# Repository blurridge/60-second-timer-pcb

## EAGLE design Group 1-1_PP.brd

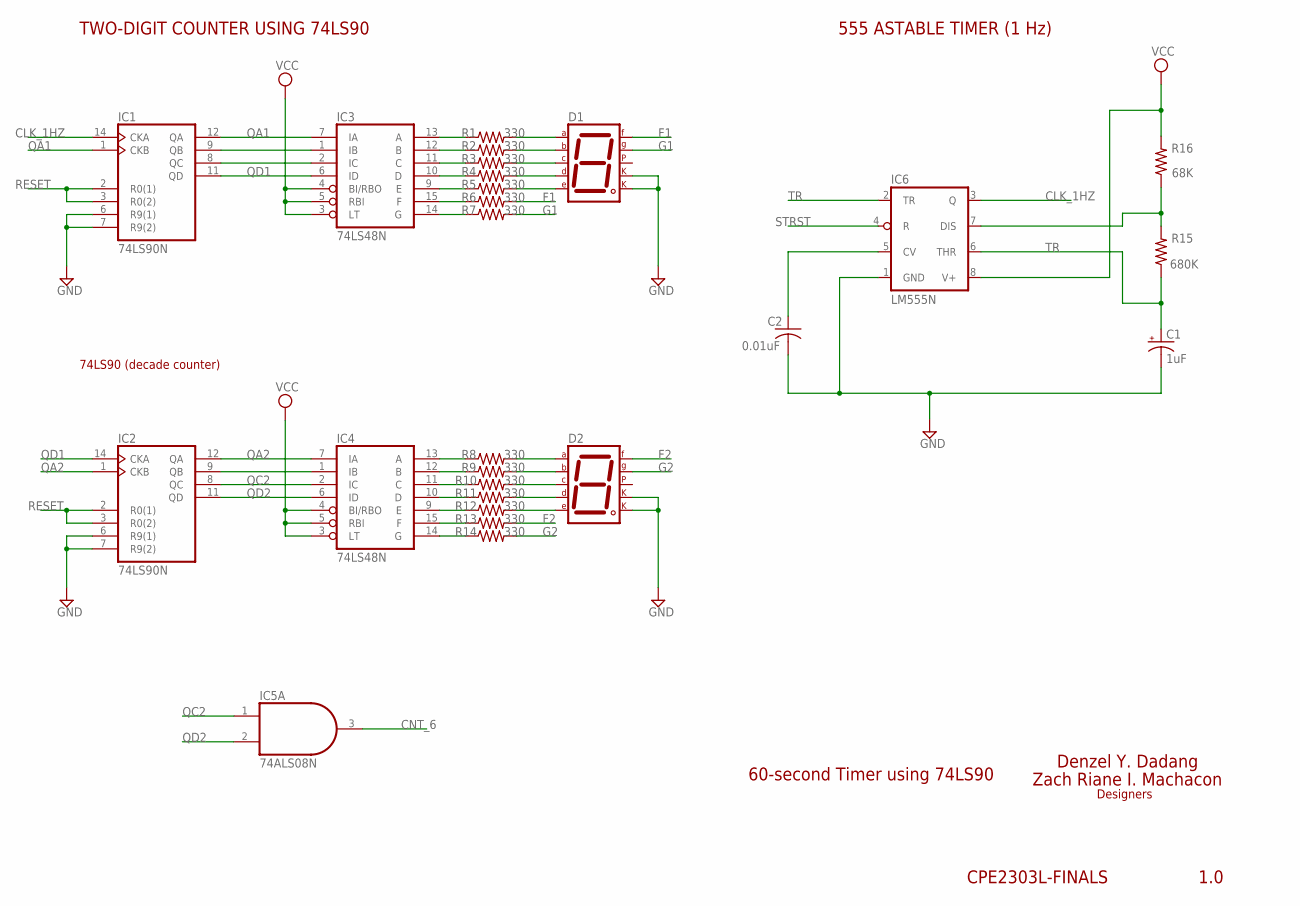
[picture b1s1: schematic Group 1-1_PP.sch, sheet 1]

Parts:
C1: 1uF; E1,8-4
C2: 0.01uF; C025-025X050
D1, D2: 7SEG-CK; 7SEG-13
IC1, IC2: 74LS90N; DIL14
IC3, IC4: 74LS48N; DIL16
IC5: 74ALS08N; DIL14
IC6: LM555N; DIL08
R1, R2, R3, R4, R5, R6, R7, R8, R9, R10, R11, R12, R13, R14: 330; 0204/7
R15: 680K; 0204/7
R16: 68K; 0204/7

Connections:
CLK_1HZ: IC1.14 (CKA), IC6.3 (Q)
CNT_6: IC5.3 (O); also elsewhere on the board
F1: D1.9 (F), R6.2
F2: D2.9 (F), R13.2
G1: D1.10 (G), R7.2
G2: D2.10 (G), R14.2
GND: C1.-, C2.2, D1.3 (CK1), D1.8 (CK2), D2.3 (CK1), D2.8 (CK2), IC1.6 (R9(1)), IC1.7 (R9(2)), IC1.10 (GND), IC2.6 (R9(1)), IC2.7 (R9(2)), IC2.10 (GND), IC3.8 (GND), IC4.8 (GND), IC5.7 (GND), IC6.1 (GND); also elsewhere on the board
unnamed: IC3.13 (A), R1.1
unnamed: IC6.7 (DIS), R15.2, R16.1
unnamed: IC1.9 (QB), IC3.1 (IB)
unnamed: C2.1, IC6.5 (CV)
unnamed: IC1.8 (QC), IC3.2 (IC)
unnamed: IC3.12 (B), R2.1
unnamed: IC3.11 (C), R3.1
unnamed: IC3.10 (D), R4.1
unnamed: IC3.9 (E), R5.1
unnamed: IC3.15 (F), R6.1
unnamed: IC3.14 (G), R7.1
unnamed: IC4.13 (A), R8.1
unnamed: IC2.9 (QB), IC4.1 (IB)
unnamed: D1.1 (E), R5.2
unnamed: D1.2 (D), R4.2
unnamed: D1.4 (C), R3.2
unnamed: D1.6 (B), R2.2
unnamed: D1.7 (A), R1.2
unnamed: IC4.12 (B), R9.1
unnamed: IC4.11 (C), R10.1
unnamed: IC4.10 (D), R11.1
unnamed: IC4.9 (E), R12.1
unnamed: IC4.15 (F), R13.1
unnamed: IC4.14 (G), R14.1
unnamed: D2.7 (A), R8.2
unnamed: D2.6 (B), R9.2
unnamed: D2.4 (C), R10.2
unnamed: D2.2 (D), R11.2
unnamed: D2.1 (E), R12.2
QA1: IC1.1 (CKB), IC1.12 (QA), IC3.7 (IA)
QA2: IC2.1 (CKB), IC2.12 (QA), IC4.7 (IA)
QC2: IC2.8 (QC), IC4.2 (IC), IC5.1 (I0)
QD1: IC1.11 (QD), IC2.14 (CKA), IC3.6 (ID)
QD2: IC2.11 (QD), IC4.6 (ID), IC5.2 (I1)
RESET: IC1.2 (R0(1)), IC1.3 (R0(2)), IC2.2 (R0(1)), IC2.3 (R0(2)); also elsewhere on the board
STRST: IC6.4 (R); also elsewhere on the board
TR: C1.+, IC6.2 (TR), IC6.6 (THR), R15.1
VCC: IC1.5 (VCC), IC2.5 (VCC), IC3.3 (LT), IC3.4 (BI/RBO), IC3.5 (RBI), IC3.16 (VCC), IC4.3 (LT), IC4.4 (BI/RBO), IC4.5 (RBI), IC4.16 (VCC), IC5.14 (VCC), IC6.8 (V+), R16.2; also elsewhere on the board

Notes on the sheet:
60-second Timer using 74LS90
Zach Riane I. Machacon
Denzel Y. Dadang
Designers
CPE2303L-FINALS
1.0
555 ASTABLE TIMER (1 Hz)
TWO-DIGIT COUNTER USING 74LS90
74LS90 (decade counter)

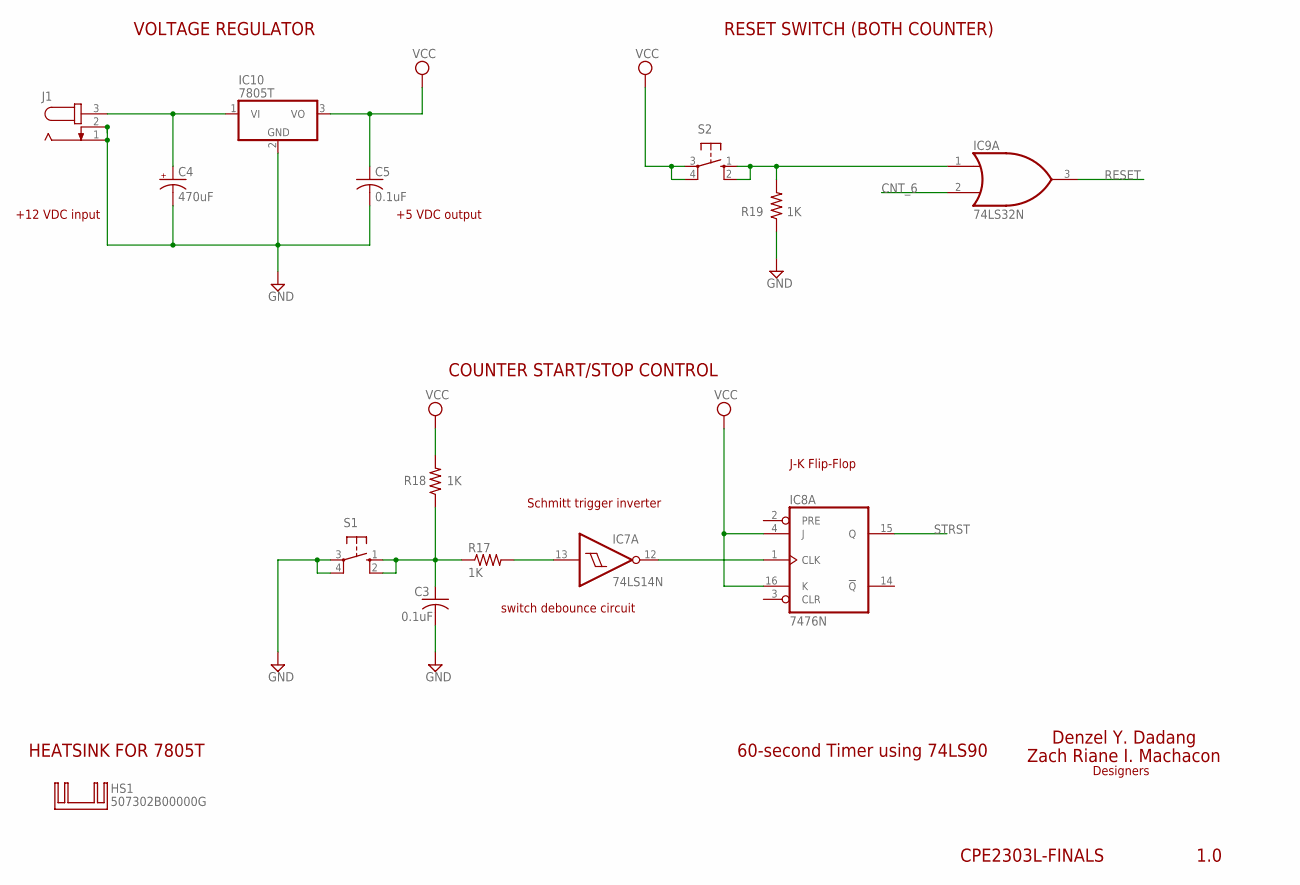
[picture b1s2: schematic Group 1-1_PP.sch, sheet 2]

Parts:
C3, C5: 0.1uF; C025-025X050
C4: 470uF; E1,8-4
HS1: 507302B00000G; TO-220H
IC7: 74LS14N; DIL14
IC8: 7476N; DIL16
IC9: 74LS32N; DIL14
IC10: 7805T; TO220H
J1: JACK-PLUG1; SPC4078
R17, R18, R19: 1K; 0204/7
S1, S2: 10-XX; B3F-10XX

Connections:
CNT_6: IC9.2 (I1); also elsewhere on the board
GND: C3.2, C4.-, C5.2, IC7.7 (GND), IC8.13 (GND), IC9.7 (GND), IC10.2 (GND), J1.1, J1.2, R19.1, S1.3, S1.4 (P1); also elsewhere on the board
unnamed: C4.+, IC10.1 (VI), J1.3
unnamed: IC7.12 (O), IC8.1 (CLK)
unnamed: IC7.13 (I), R17.2
unnamed: C3.1, R17.1, R18.1, S1.1 (S), S1.2 (S1)
unnamed: IC9.1 (I0), R19.2, S2.1 (S), S2.2 (S1)
RESET: IC9.3 (O); also elsewhere on the board
STRST: IC8.15 (Q); also elsewhere on the board
VCC: C5.1, IC7.14 (VCC), IC8.4 (J), IC8.5 (VCC), IC8.16 (K), IC9.14 (VCC), IC10.3 (VO), R18.2, S2.3, S2.4 (P1); also elsewhere on the board

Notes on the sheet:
60-second Timer using 74LS90
Zach Riane I. Machacon
Denzel Y. Dadang
Designers
CPE2303L-FINALS
1.0
VOLTAGE REGULATOR
+12 VDC input
+5 VDC output
COUNTER START/STOP CONTROL
RESET SWITCH (BOTH COUNTER)
switch debounce circuit
Schmitt trigger inverter
J-K Flip-Flop
HEATSINK FOR 7805T

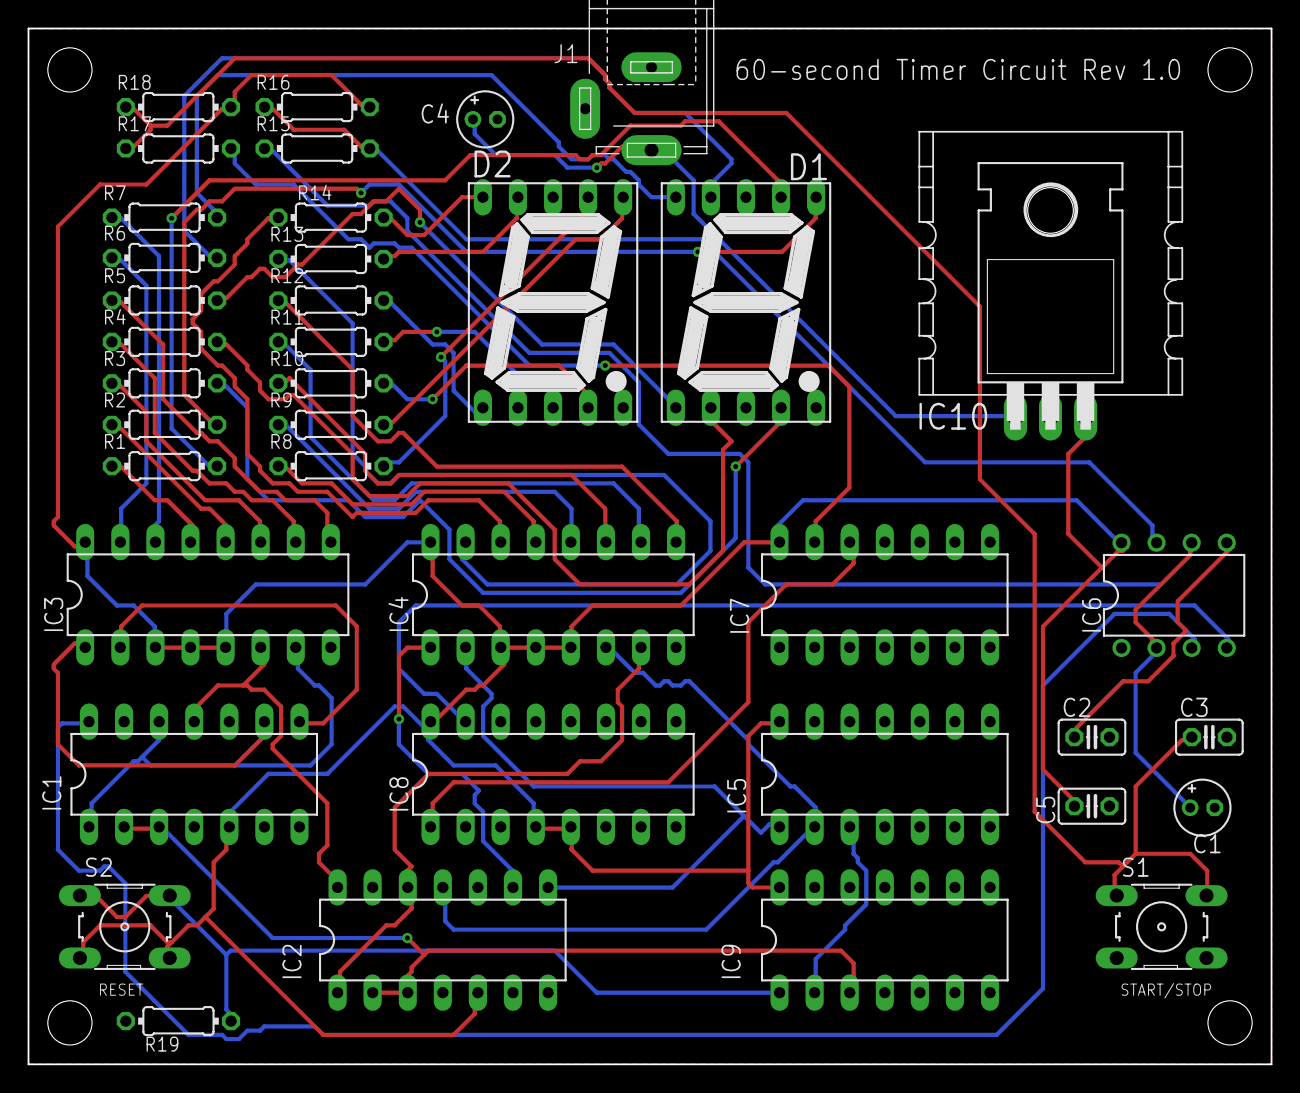
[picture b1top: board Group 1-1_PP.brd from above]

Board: 2 copper layers, 90.0 x 75.0 mm, 40 parts (0 on the bottom side), 50 nets.

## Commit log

2023-07-20 [Zach] initial commit; to finish heatsink
2023-07-21 [Zach] Added heatsink
2023-07-21 revised file names and edited heatsink
2023-07-21 [Zach] Edited heatsink and 7805 3D Model
2023-07-21 [Zach] Changed heatsink hole
2023-07-21 MANAAAAAAAAAAAAAAAAAAAA
2023-07-21 [Zach] Updated lbrs for regulator visibility
2023-07-21 [Zach] Rearranged IC labels
2023-07-26 [Zach] Changed track widths
